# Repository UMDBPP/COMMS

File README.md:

# COMMS
Communication Over Microwave Mesh

End goal of project is to have complete access to retrive data from and command every payload on the line from a single ground point.

Current design ideology is the use of low power low data rate radios to communicate with a central node that has a "bigger" radio to send all the data to the ground.

Due to size, power and my general insanity radios are being custom designed

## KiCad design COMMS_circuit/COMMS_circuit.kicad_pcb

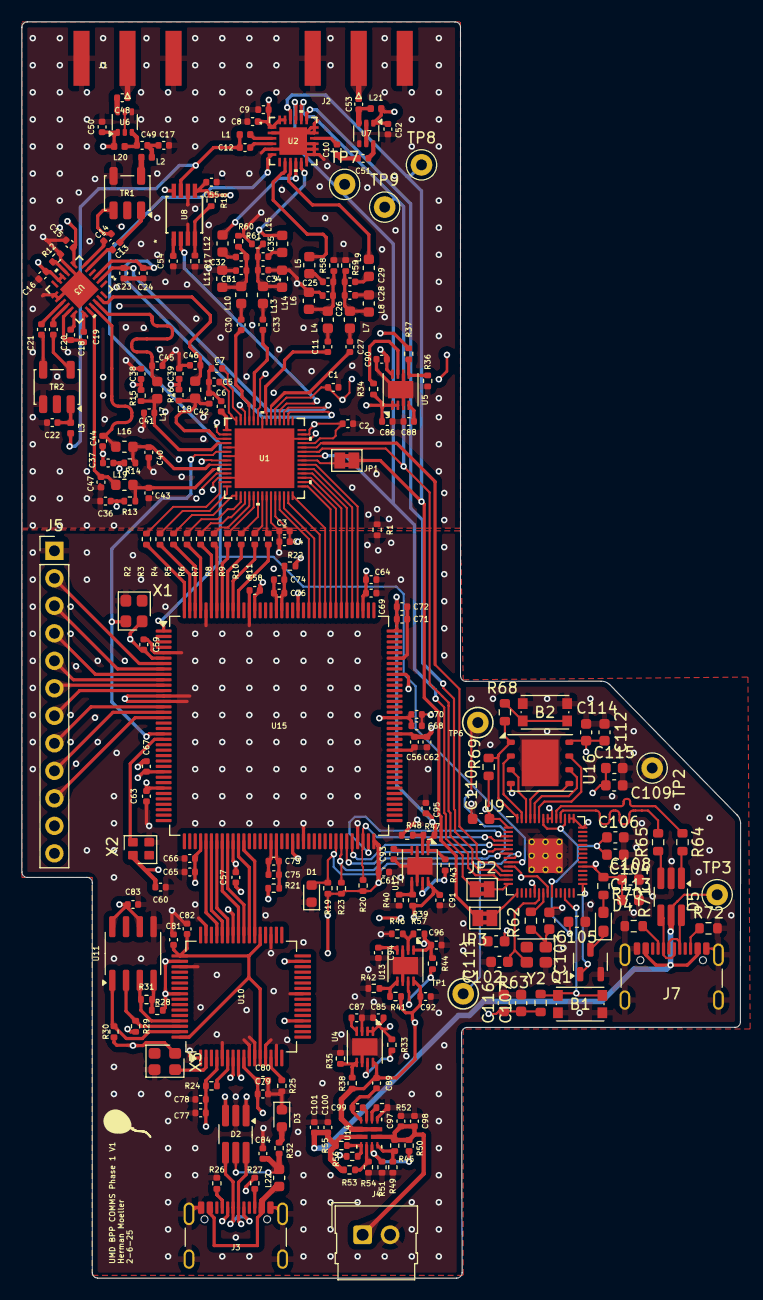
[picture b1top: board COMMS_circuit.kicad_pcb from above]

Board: 4 copper layers, 66.4 x 116.0 mm, 254 parts (0 on the bottom side), 198 nets.

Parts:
B1, B2: KMR2; SW_Push_1P1T_NO_CK_KMR2
C1, C3: 2.2uF; C_0402_1005Metric
C2, C4, C16, C18, C19, C23, C24: 0.1uF; C_0402_1005Metric
C5, C6, C7: 0.33uF; C_0402_1005Metric
C8, C87, C88, C93, C94: 1nF; C_0402_1005Metric
C9: 4.7uF; C_0402_1005Metric
C10: 10uF; C_0402_1005Metric
C11, C27, C30, C33: 1.6p; C_0402_1005Metric
C12: 3pF; C_0402_1005Metric
C13, C14, C15, C20, C21: 0.01uF; C_0402_1005Metric
C17: 1pF; C_0402_1005Metric
C22: 1.5pF; C_0402_1005Metric
C25, C29, C32, C35: 10p; C_0402_1005Metric
C26, C28, C31, C34: 3p; C_0402_1005Metric
C36, C37, C38, C39, C61, C65, C72: 1u; C_0402_1005Metric
C40, C41, C42, C43: 43p; C_0402_1005Metric
C44, C45, C46, C47: 6.8p; C_0402_1005Metric
C48, C49, C51, C53: 100p; C_0402_1005Metric
C50, C52: 1000p; C_0402_1005Metric
C54, C55: 330n; C_0402_1005Metric
C56, C57, C58, C59, C62, C66, C67, C68, C69, C75, C76, C77, C80, C82, C83: 0.1u; C_0402_1005Metric
C60, C64, C71, C73, C74: 10u; C_0402_1005Metric
C63, C70: 0.01u; C_0402_1005Metric
C78, C79, C81, C84: 4.7u; C_0402_1005Metric
C85, C86, C89, C90, C91, C92, C95, C96, C97, C99, C100: 1uF; C_0402_1005Metric
C98, C101: 100nF; C_0402_1005Metric
C102, C103: 10pF; C_0603_1608Metric
C104, C105, C108, C109, C110, C111, C113, C114, C115, C116: 100nF; C_0603_1608Metric
C106, C107: 1uF; C_0603_1608Metric
C112: 10uF; C_0603_1608Metric
D1, D3: LED; LED_0603_1608Metric
D2, D5: USBLC6-2SC6; TSOT-23-6_HandSoldering
D4: LED; D_0603_1608Metric_Pad1.05x0.95mm_HandSolder
J1, J2: SMA; SMA_Amphenol_132289_EdgeMount
J3: USB_C_Receptacle_USB2.0_14P; USB_C_Receptacle_GCT_USB4105-xx-A_16P_TopMnt_Horizontal
J4: Conn_01x02_Pin; Molex_SL_171971-0002_1x02_P2.54mm_Vertical
J5: Conn_01x12_Pin; PinHeader_1x12_P2.54mm_Vertical
J7: USB_C_Receptacle_USB2.0; USB_C_Receptacle_GCT_USB4105-xx-A_16P_TopMnt_Horizontal
JP1, JP2, JP3: Jumper_2_Bridged; SolderJumper-2_P1.3mm_Bridged2Bar_Pad1.0x1.5mm
L1: 5.6nH; L_0402_1005Metric
L2: 4nH; L_0402_1005Metric
L3: 3nH; L_0402_1005Metric
L4, L7, L10, L13: 6.8u; L_0603_1608Metric
L5, L9, L12, L15: 1.1u; L_0603_1608Metric
L6, L8, L11, L14: 3.6u; L_0603_1608Metric
L16, L17, L18, L19: 360n; L_0603_1608Metric
L20, L21: 100n; L_0402_1005Metric
L22: 600 ohm 500 mA; L_0603_1608Metric
Q1: IRLML0060TRPBF; SOT-23-3
R1: 3; R_0402_1005Metric
R2, R3, R4, R5, R6, R7, R8, R9, R10, R11, R13, R14, R15, R16, R21, R22: 100; R_0402_1005Metric
R12: 0; R_0402_1005Metric
R17: 1000; R_0402_1005Metric
R18: 1300; R_0402_1005Metric
R19: 650; R_0402_1005Metric
R20, R23, R28, R29, R30: 10k; R_0402_1005Metric
R24, R31, R32: 2.2k; R_0402_1005Metric
R25: 12k; R_0402_1005Metric
R26, R27: 5.1k; R_0402_1005Metric
R33, R34, R35, R36, R37, R38, R39, R40, R41, R42, R43, R44, R46: 100k; R_0402_1005Metric
R45: 18.2k; R_0402_1005Metric
R47: 31.6k; R_0402_1005Metric
R48: 30.1k; R_0402_1005Metric
R49, R51, R54, R56: 5k; R_0402_1005Metric
R50: 63.4k; R_0402_1005Metric
R52: 21.5k; R_0402_1005Metric
R53: 23.7k; R_0402_1005Metric
R55: 10.2k; R_0402_1005Metric
R57: 330; R_0402_1005Metric
R58, R59, R60, R61: 1k; R_0402_1005Metric
R62, R68: 1k; R_0603_1608Metric
R63, R69: 10k; R_0603_1608Metric
R64, R65: 27; R_0603_1608Metric
R70: 590; R_0603_1608Metric
R71, R72: 5.1k; R_0603_1608Metric
TP1, TP2, TP3, TP6, TP7, TP8, TP9: TestPoint; TestPoint_Keystone_5000-5004_Miniature
TR1, TR2: TC1-1-13M+; Transformer_MiniCircuits_AT224-1A
U1: max19713etn+; 21-0144_T5677&plus_2_MXM
U2: LTC5599IUF-PBF; QFN-24_UF_LIT
U3: LTC5584IUF-PBF; QFN-24_UF_LIT
U4: ADP7105ACPZ-3.3-R7; LFCSP-8-1EP_3x3mm_P0.5mm_EP1.6x2.34mm
U5: ADP7105ACPZ-5.0-R7; LFCSP-8-1EP_3x3mm_P0.5mm_EP1.6x2.34mm
U6, U7: NSVG3117SG6T1G; SOT-363_SC-70-6
U8: MAX2754EUA+; 21-0036K_MXM
U9: RP2040; RP2040-QFN-56
U10: FT2232HL; LQFP-64_10x10mm_P0.5mm
U11: 93LC56; SOIC-8_3.9x4.9mm_P1.27mm
U12, U13: ADP7105ACPZ-R7; LFCSP-8-1EP_3x3mm_P0.5mm_EP1.6x2.34mm
U14: TPS2121RUXR; TPS2121
U15: ICE40HX4K-TQ144; TQFP-144_20x20mm_P0.5mm
U16: W25Q64JVZP; WSON-8-1EP_6x5mm_P1.27mm_EP3.4x4.3mm
X1: SIT8918AE-13-33N-45; Oscillator_SMD_SiTime_PQFD-4L_2.5x2mm
X2: SIT8925BA-78-25N-125.000000; Oscillator_SMD_SiTime_PQFD-4L_2x1.6mm
X3: SIT9003AI-13-33DB-12.00000Y; Oscillator_SMD_SiTime_PQFD-4L_2.5x2mm
Y2: 12MHz; Crystal_SMD_2520-4Pin_2.5x2.0mm

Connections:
+1V2: C64.2, C65.2, C66.2, C67.2, C68.2, C69.2, C70.2, C96.1, R21.2, R22.2, R44.1, R57.2, U13.1 (VOUT), U15.27 (VCC), U15.40 (VCC), U15.92 (VCC), U15.111 (VCC)
+2V5: C71.2, C72.2, C95.1, R43.1, R47.2, U12.1 (VOUT), U15.108 (VPP_2V5)
+3V3: C1.1, C2.1, C3.1, C4.1, C8.1, C9.1, C55.2, C56.2, C57.2, C58.2, C59.2, C60.2, C61.2, C62.2, C63.2, C77.1, C78.1, C79.1, C80.1, C83.1, C85.1, C107.1, C108.1, C109.1, C110.1, C111.1, C112.1, C113.1, C114.1, C115.1, C116.1, J5.11, R18.1, R19.1, R20.1, R23.1, R24.1, R28.2, R29.2, R30.2, R33.1, R63.1, R69.1, R70.1, U1.2 (VDD), U1.8 (VDD), U1.11 (VDD), U1.24 (OVDD), U1.39 (VDD), U1.41 (VDD), U1.47 (VDD), U1.51 (VDD), U1.54 (REFIN), U2.1 (VCTRL), U2.23 (EN), U2.24 (VCC), U4.1 (VOUT), U4.2 (SENSE), U8.5 (*SHDN), U8.8 (VCC), U9.1 (IOVDD), U9.10 (IOVDD), U9.22 (IOVDD), U9.33 (IOVDD), U9.42 (IOVDD), U9.43 (ADC_AVDD), U9.44 (VREG_IN), U9.48 (USB_VDD), U9.49 (IOVDD), U10.4 (VPHY), U10.9 (VPLL), U10.20 (VCCIO), U10.31 (VCCIO), U10.42 (VCCIO), U10.50 (VREGIN), U10.56 (VCCIO), U11.6 (ORG), U11.8 (VCC), U15.6 (VCCIO_3), U15.30 (VCCIO_3), U15.46 (VCCIO_2), U15.57 (VCCIO_2), U15.72 (VCC_SPI), U15.89 (VCCIO_1), U15.100 (VCCIO_1), U15.123 (VCCIO_0), U15.131 (VCCIO_0), U16.8 (VCC), X1.4 (VDD), X2.4 (VDD), X3.4 (VDD)
+5V: C15.2, C16.2, C36.1, C37.1, C38.1, C39.1, C50.2, C52.2, C86.1, J5.12, L20.1, L21.1, R13.1, R14.1, R15.1, R16.1, R34.1, U3.7 (EN), U3.10 (VCC), U3.11 (EDC), U5.1 (VOUT), U5.2 (SENSE), U6.1 (vcc), U7.1 (vcc)
/AD0: R2.1, U15.144 (IOT_222)
/AD1: R3.1, U15.143 (IOT_221)
/AD2: R4.1, U15.142 (IOT_220)
/AD3: R5.1, U15.141 (IOT_219)
/AD4: R6.1, U15.139 (IOT_217)
/AD5: R7.1, U15.138 (IOT_216)
/AD6: R8.1, U15.137 (IOT_215)
/AD7: R9.1, U15.136 (IOT_214)
/AD8: R10.1, U15.135 (IOT_213)
/AD9: R11.1, U15.134 (IOT_212)
/CTSn: U10.43 (BDBUS4), U15.43 (IOB_71)
/D1: Q1.1 (G), U9.29 (GPIO18)
/D+: D5.6 (L1), J7.A6 (D+), J7.B6 (D+)
/D-: D5.4 (L2), J7.A7 (D-), J7.B7 (D-)
/DA0: U1.25 (DA0), U15.121 (IOT_181)
/DA1: U1.26 (DA1), U15.120 (IOT_179)
/DA2: U1.27 (DA2), U15.119 (IOT_178)
/DA3: U1.28 (DA3), U15.118 (IOT_177)
/DA4: U1.29 (DA4), U15.117 (IOT_174)
/DA5: U1.30 (DA5), U15.116 (IOT_173)
/DA6: U1.31 (DA6), U15.115 (IOT_172)
/DA7: U1.32 (DA7), U15.114 (IOT_171)
/DA8: U1.33 (DA8), U15.113 (IOT_170)
/DA9: U1.34 (DA9), U15.112 (IOT_169)
/DCDn: U10.45 (BDBUS6), U15.41 (IOB_63)
/DSRn: U10.44 (BDBUS5), U15.42 (IOB_64)
/DTRn: U10.40 (BDBUS2), U15.45 (IOB_73)
/Data_clk: U1.6 (CLK), U15.20 (IOL_13B_GBIN7), X1.3 (OUT)
/HOST_MISO: U9.6 (GPIO4), U15.67 (IOB_105_SDO)
/HOST_MOSI: U9.5 (GPIO3), U15.68 (IOB_106_SDI)
/HOST_SCK: R20.2, U9.4 (GPIO2), U15.70 (IOB_107_SCK)
/HOST_SS: U9.3 (GPIO1), U15.71 (IOB_108_SS)
/ICE_CDONE: D1.2 (A), R19.2, TP1.1, U9.8 (GPIO6), U15.65 (CDONE)
/ICE_CRESET: R23.2, TP6.1, U9.7 (GPIO5), U15.66 (~CRESET)
/Payload_Payload_radio_module/BBMI: L9.2, U2.9 (BBMI)
/Payload_Payload_radio_module/BBMQ: L15.2, U2.11 (BBMQ)
/Payload_Payload_radio_module/BBPI: L5.2, U2.8 (BBPI)
/Payload_Payload_radio_module/BBPQ: L12.2, U2.10 (BBPQ)
/Payload_Payload_radio_module/DCO_I: C24.1, U1.44 (DAC3), U3.3 (DCOI)
/Payload_Payload_radio_module/DCO_Q: C23.1, U1.45 (DAC2), U3.2 (DCOQ)
/Payload_Payload_radio_module/I+: C46.1, L18.1, U3.23 (I+)
/Payload_Payload_radio_module/I-: C45.1, L17.1, U3.22 (I-)
/Payload_Payload_radio_module/LO: C12.1, L1.1, L3.2, U8.7 (OUT)
/Payload_Payload_radio_module/LO_TUNE: U1.46 (DAC1), U8.2 (TUNE)
/Payload_Payload_radio_module/Q+: C44.1, L16.1, U3.21 (Q+)
/Payload_Payload_radio_module/Q-: C47.1, L19.1, U3.20 (Q-)
/Payload_Payload_radio_module/RX_I_N: C41.1, L17.2, R15.2, U1.4 (IAN)
/Payload_Payload_radio_module/RX_I_P: C42.1, L18.2, R16.2, U1.3 (IAP)
/Payload_Payload_radio_module/RX_Q_N: C43.1, L19.2, R13.2, U1.10 (QAP)
/Payload_Payload_radio_module/RX_Q_P: C40.1, L16.2, R14.2, U1.9 (QAN)
/Payload_Payload_radio_module/RX_RF: C17.1, C49.1, L2.1
/Payload_Payload_radio_module/TX_I_N: C27.1, U1.48 (IDN)
/Payload_Payload_radio_module/TX_I_P: C11.1, U1.49 (IDP)
/Payload_Payload_radio_module/TX_Q_N: C33.1, U1.52 (QDN)
/Payload_Payload_radio_module/TX_Q_P: C30.1, U1.53 (QDP)
/Payload_Payload_radio_module/TX_RF: C10.2, C51.2
/Power/BATT_POWER: C97.1, C98.1, J4.1, R45.2, R50.2, U14.7 (IN1)
/Power/VIN: C89.1, C90.1, C91.1, C92.1, R37.2, R38.2, R39.2, R41.2, U4.8 (VIN), U5.8 (VIN), U12.8 (VIN), U13.8 (VIN), U14.1 (OUT), U14.8 (OUT)
/QSPI_SCLK: U9.52 (QSPI_SCLK), U16.6 (CLK)
/QSPI_SD0: U9.53 (QSPI_SD0), U16.5 (DI(IO0))
/QSPI_SD1: U9.55 (QSPI_SD1), U16.2 (DO(IO1))
/QSPI_SD2: U9.54 (QSPI_SD2), U16.3 (IO2)
/QSPI_SD3: U9.51 (QSPI_SD3), U16.7 (IO3)
/QSPI_SS: R68.2, R69.2, U9.56 (QSPI_SS), U16.1 (~CS)
/RS232_RX_TTL: U10.38 (BDBUS0), U15.48 (IOB_80)
/RS232_TX_TTL: U10.39 (BDBUS1), U15.47 (IOB_79)
/RTSn: U10.41 (BDBUS3), U15.44 (IOB_72)
/SPI_CLK: TP9.1, U1.37 (SCLK), U2.20 (SCLK), U9.13 (GPIO10)
/SPI_CS_FE: U1.38 (*CS/WAKE), U9.11 (GPIO8)
/SPI_CS_M: U2.19 (CSB), U9.12 (GPIO9)
/SPI_SDI: JP2.2 (B), TP7.1, U1.36 (DIN), U2.21 (SDI)
/SPI_SDO: JP1.2 (B), JP3.2 (B), TP8.1, U2.22 (SDO)
/SYS_clk: U15.21 (IOL_14A_GBIN6), X2.3 (OUT)
/TTCK: U2.6 (TTCK), U9.9 (GPIO7), U15.1 (IOL_2A)
/USB/DM: D2.1 (L1), U10.7 (DM)
/USB/DP: D2.3 (L2), U10.8 (DP)
/USB/F_CS: R30.1, U10.63 (EECS), U11.1 (CS)
/USB_D+: D5.1 (L1), R64.2
/USB_D-: D5.3 (L2), R65.2
AGND: C1.2, C2.2, C5.2, C6.1, C7.2, C8.2, C9.2, C15.1, C16.1, C17.2, C22.2, C23.2, C24.2, C26.1, C28.1, C31.1, C34.1, C36.2, C37.2, C38.2, C39.2, C40.2, C41.2, C42.2, C43.2, C44.2, C45.2, C46.2, C47.2, C50.1, C52.1, C54.1, C55.1, C86.2, C88.2, C90.2, J1.2 (Ext), J2.2 (Ext), L6.2, L8.2, L11.2, L14.2, R1.1, R12.2, R17.2, R36.1, R58.2, R59.2, R60.2, R61.2, TR1.4, TR2.3, U1.5 (GND), U1.7 (GND), U1.12 (GND), U1.40 (GND), U1.50 (GND), U1.57 (EP), U2.2 (GND), U2.5 (GND), U2.12 (GND), U2.13 (GNDRF), U2.14 (GNDRF), U2.15 (GNDRF), U2.17 (GNDRF), U2.18 (GNDRF), U2.25 (GND), U3.8 (GND), U3.13 (GND), U3.14 (GND), U3.25 (EPAD), U5.3 (GND), U5.6 (GND), U5.9 (GND), U6.2 (gnd), U6.4 (gnd), U6.5 (gnd), U7.2 (gnd), U7.4 (gnd), U7.5 (gnd), U8.3 (GND1), U8.6 (GND2)
DGND: B1.1, B2.1, C3.2, C4.2, C56.1, C57.1, C58.1, C59.1, C60.1, C61.1, C62.1, C63.1, C64.1, C65.1, C66.1, C67.1, C68.1, C69.1, C70.1, C71.1, C72.1, C77.2, C78.2, C79.2, C80.2, C81.2, C82.2, C83.2, C84.2, C85.2, C87.2, C89.2, C91.2, C92.2, C93.2, C94.2, C95.2, C96.2, C97.2, C98.2, C99.1, C100.2, C101.2, C102.1, C103.1, C104.2, C105.2, C106.2, C107.2, C108.2, C109.2, C110.2, C111.2, C112.2, C113.2, C114.2, C115.2, C116.2, D1.1 (K), D2.2 (VN), D3.1 (K), D5.2 (VN), J3.A1 (GND), J3.A12 (GND), J3.B1 (GND), J3.B12 (GND), J3.S1 (SHIELD), J4.2, J5.1, J7.A1 (GND), J7.A12 (GND), J7.B1 (GND), J7.B12 (GND), J7.S1 (SHIELD), Q1.2 (S), R1.2, R25.1, R26.2, R27.2, R35.1, R40.1, R42.1, R46.1, R48.1, R49.1, R51.1, R52.2, R54.1, R56.1, R71.2, R72.2, TP2.1, U1.23 (OGND), U4.3 (GND), U4.6 (GND), U4.9 (GND), U9.19 (TESTEN), U9.57 (GND), U10.1 (GND), U10.5 (GND), U10.10 (AGND), U10.11 (GND), U10.13 (TEST), U10.15 (GND), U10.25 (GND), U10.35 (GND), U10.47 (GND), U10.51 (GND), U11.5 (GND), U12.3 (GND), U12.6 (GND), U12.9 (GND), U13.3 (GND), U13.6 (GND), U13.9 (GND), U14.9 (ST), U14.12 (GND), U15.5 (GND), U15.13 (GND), U15.14 (GND), U15.59 (GND), U15.69 (GND), U15.86 (GND), U15.103 (GND), U15.132 (GND), U15.140 (GND), U16.4 (GND), U16.9 (EP), X1.2 (GND), X2.2 (GND), X3.2 (GND), Y2.4
unnamed: B2.2, R68.1
unnamed: C11.2, L4.1
unnamed: C13.1, TR1.1
unnamed: C14.1, TR1.3
unnamed: C20.2, TR2.6
unnamed: C21.2, TR2.4
unnamed: C22.1, L3.1, TR2.1
unnamed: C25.1, C26.2, L4.2, L6.1, R58.1
unnamed: C25.2, L5.1
unnamed: C27.2, L7.1
unnamed: C28.2, C29.1, L7.2, L8.1, R59.1
unnamed: C29.2, L9.1
unnamed: C30.2, L10.1
unnamed: C31.2, C32.1, L10.2, L11.1, R60.1
unnamed: C32.2, L12.1
unnamed: C33.2, L13.1
unnamed: C34.2, C35.1, L13.2, L14.1, R61.1
unnamed: C35.2, L15.1
unnamed: C103.2, R62.1, Y2.1
unnamed: D2.6 (L1), J3.A7 (D-), J3.B7 (D-)
unnamed: D2.4 (L2), J3.A6 (D+), J3.B6 (D+)
unnamed: C84.1, D2.5 (VP), L22.1, R32.1
unnamed: D3.2 (A), R32.2
unnamed: D4.2 (A), R70.2
unnamed: D4.1 (K), Q1.3 (D)
unnamed: C48.1, J1.1 (In)
unnamed: C53.1, J2.1 (In)
unnamed: J3.A5 (CC1), R26.1
unnamed: J3.B5 (CC2), R27.1
unnamed: J3.A4 (VBUS), J3.A9 (VBUS), J3.B4 (VBUS), J3.B9 (VBUS), L22.2
unnamed: J5.2, U15.7 (IOL_4A)
unnamed: J5.3, U15.8 (IOL_4B)
unnamed: J5.4, U15.9 (IOL_5A)
unnamed: J5.5, U15.10 (IOL_5B)
unnamed: J5.6, U15.11 (IOL_8A)
unnamed: J5.7, U15.12 (IOL_8B)
unnamed: J5.8, U15.15 (IOL_10A)
unnamed: J5.9, U15.16 (IOL_10B)
unnamed: J5.10, U15.17 (IOL_12A)
unnamed: J7.A5 (CC1), R71.1
unnamed: J7.B5 (CC2), R72.1
unnamed: JP1.1 (A), U1.35 (DOUT)
unnamed: JP2.1 (A), U9.14 (GPIO11)
unnamed: JP3.1 (A), U9.15 (GPIO12)
unnamed: L2.2, TR1.6
unnamed: R2.2, U1.13 (AD0)
unnamed: R3.2, U1.14 (AD1)
unnamed: R4.2, U1.15 (AD2)
unnamed: R5.2, U1.16 (AD3)
unnamed: R6.2, U1.17 (AD4)
unnamed: R7.2, U1.18 (AD5)
unnamed: R8.2, U1.19 (AD6)
unnamed: R9.2, U1.20 (AD7)
unnamed: R10.2, U1.21 (AD8)
unnamed: R11.2, U1.22 (AD9)
unnamed: C7.1, U1.55 (COM)
unnamed: C5.1, U1.56 (REFN)
unnamed: C6.2, U1.1 (REFP)
unnamed: C12.2, U2.4 (LOC)
unnamed: L1.2, U2.3 (LOL)
unnamed: C10.1, U2.16 (RF)
unnamed: C19.1, U3.19 (CMI)
unnamed: C18.2, U3.18 (CMQ)
unnamed: C21.1, U3.15 (LO+)
unnamed: C20.1, U3.16 (LO-)
unnamed: C13.2, U3.5 (RF+)
unnamed: C14.2, U3.6 (RF-)
unnamed: R12.1, U3.9 (VBIAS)
unnamed: C18.1, C19.2, U3.17 (VCAP)
unnamed: R35.2, R38.1, U4.5 (EN/UVLO)
unnamed: R33.2, U4.7 (PG)
unnamed: C87.1, U4.4 (SS)
unnamed: R36.2, R37.1, U5.5 (EN/UVLO)
unnamed: R34.2, U5.7 (PG)
unnamed: C88.1, U5.4 (SS)
unnamed: C48.2, U6.6 (in)
unnamed: C49.2, L20.2, U6.3 (out)
unnamed: C51.1, U7.6 (in)
unnamed: C53.2, L21.2, U7.3 (out)
unnamed: R17.1, R18.2, U8.4 (MOD)
unnamed: C54.2, U8.1 (VREG)
unnamed: B1.2, R63.2, U9.26 (RUN)
unnamed: R65.1, U9.46 (USB_DM)
unnamed: R64.1, U9.47 (USB_DP)
unnamed: C104.1, C105.1, C106.1, U9.23 (DVDD), U9.45 (VREG_VOUT), U9.50 (DVDD)
unnamed: C102.2, U9.20 (XIN), Y2.3
unnamed: R62.2, U9.21 (XOUT)
unnamed: R29.1, U10.62 (EECLK), U11.2 (SCLK)
unnamed: R31.1, U10.61 (EEDATA), U11.3 (DI)
unnamed: U10.2 (OSCI), X3.3 (OUT)
unnamed: R24.2, U10.6 (REF)
unnamed: R25.2, U10.14 (~RESET)
unnamed: R28.1, R31.2, U11.4 (DO)
unnamed: R39.1, R40.2, U12.5 (EN/UVLO)
unnamed: R43.2, U12.7 (PG)
unnamed: R47.1, R48.2, U12.2 (SENSE/ADJ)
unnamed: C93.1, U12.4 (SS)
unnamed: R41.1, R42.2, U13.5 (EN/UVLO)
unnamed: R44.2, U13.7 (PG)
unnamed: R46.2, R57.1, U13.2 (SENSE/ADJ)
unnamed: C94.1, U13.4 (SS)
unnamed: R55.1, R56.2, U14.3 (CP2)
unnamed: R52.1, U14.10 (ILM)
unnamed: R50.1, R51.2, U14.5 (OV1)
unnamed: R53.1, R54.2, U14.4 (OV2)
unnamed: R45.1, R49.2, U14.6 (PR1)
unnamed: C99.2, U14.11 (SS)
unnamed: C73.1, C75.1, U15.53 (GNDPLL0)
unnamed: C74.1, C76.1, U15.127 (GNDPLL1)
unnamed: C73.2, C75.2, R21.1, U15.54 (VCCPLL0)
unnamed: C74.2, C76.2, R22.1, U15.126 (VCCPLL1)
VBUS: C100.1, C101.1, D5.5 (VP), J7.A4 (VBUS), J7.A9 (VBUS), J7.B4 (VBUS), J7.B9 (VBUS), R53.2, R55.2, TP3.1, U14.2 (IN2)
VCC: C81.1, C82.1, U10.12 (VCORE), U10.37 (VCORE), U10.49 (VREGOUT), U10.64 (VCORE)

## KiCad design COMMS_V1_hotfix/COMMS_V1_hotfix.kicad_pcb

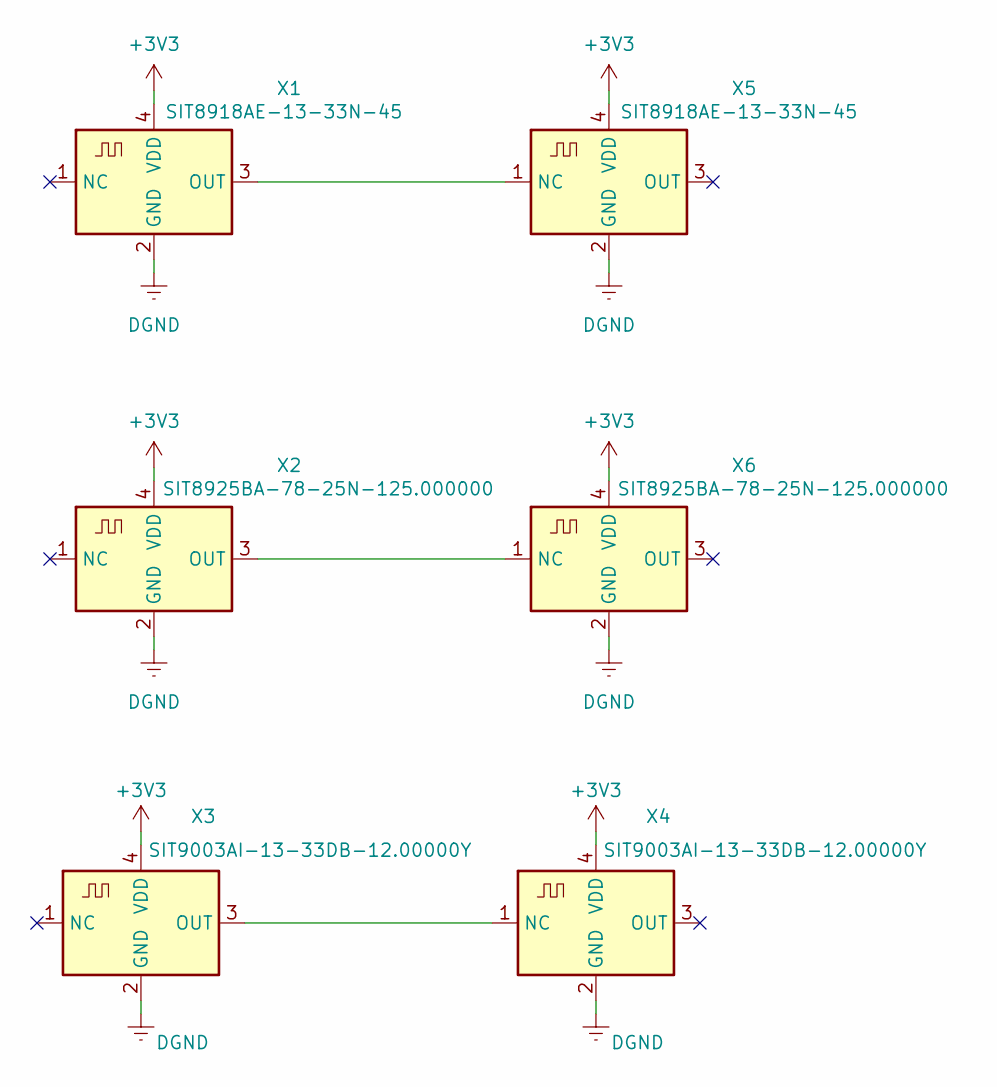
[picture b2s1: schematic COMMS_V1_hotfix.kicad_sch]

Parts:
X1, X5: SIT8918AE-13-33N-45; Oscillator_SMD_SiTime_PQFD-4L_2.5x2mm
X2, X6: SIT8925BA-78-25N-125.000000; Oscillator_SMD_SiTime_PQFD-4L_2x1.6mm
X3, X4: SIT9003AI-13-33DB-12.00000Y; Oscillator_SMD_SiTime_PQFD-4L_2.5x2mm

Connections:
+3V3: X1.4 (VDD), X2.4 (VDD), X3.4 (VDD), X4.4 (VDD), X5.4 (VDD), X6.4 (VDD)
DGND: X1.2 (GND), X2.2 (GND), X3.2 (GND), X4.2 (GND), X5.2 (GND), X6.2 (GND)
unnamed: X1.3 (OUT), X5.1 (NC)
unnamed: X2.3 (OUT), X6.1 (NC)
unnamed: X3.3 (OUT), X4.1 (NC)

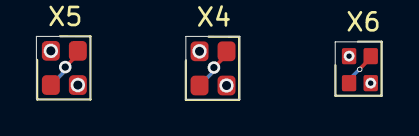
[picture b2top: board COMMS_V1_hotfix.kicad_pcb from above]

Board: 2 copper layers, 19.2 x 3.5 mm, 6 parts (0 on the bottom side), 5 nets.

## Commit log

2025-02-04 First commit yes I should have done this to begin with
2025-02-04 Adding the actual files
2025-02-04 Changes I missed cause id been staring at it to long
2025-04-04 testing opsec update
2025-04-04 Cleaning(adding manuals to the git ignore)
2025-04-04 Removing git ignored files
2025-11-25 Hotfix for first board rev and saving previous interation for next
2025-11-25 fix all noticed problems
2026-02-17 Stick a RP2040 on the side and see if we can program an FPGA with it
2026-02-20 switching the VBUS to RP2040 USB cause its more sensical
